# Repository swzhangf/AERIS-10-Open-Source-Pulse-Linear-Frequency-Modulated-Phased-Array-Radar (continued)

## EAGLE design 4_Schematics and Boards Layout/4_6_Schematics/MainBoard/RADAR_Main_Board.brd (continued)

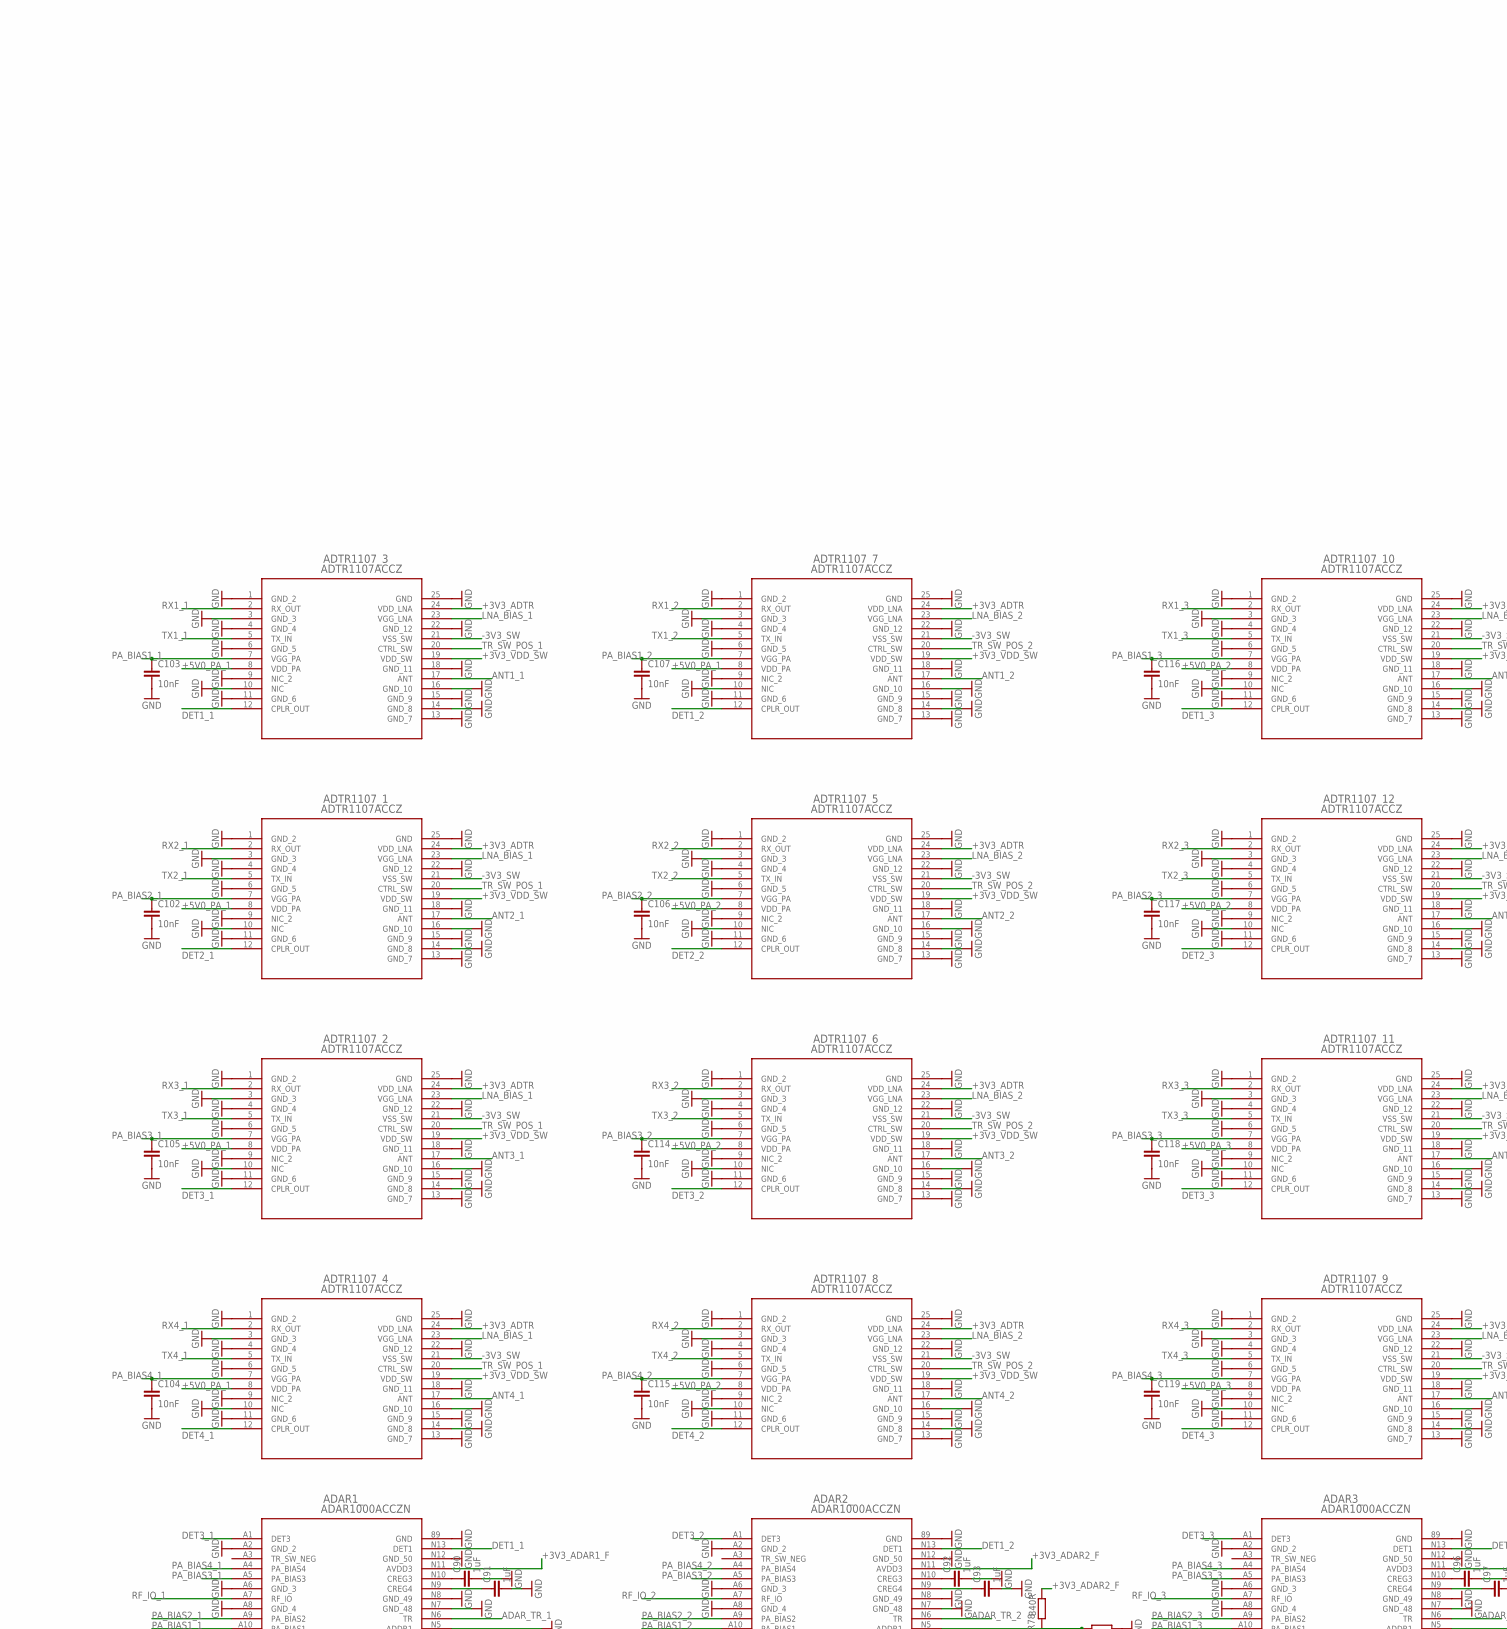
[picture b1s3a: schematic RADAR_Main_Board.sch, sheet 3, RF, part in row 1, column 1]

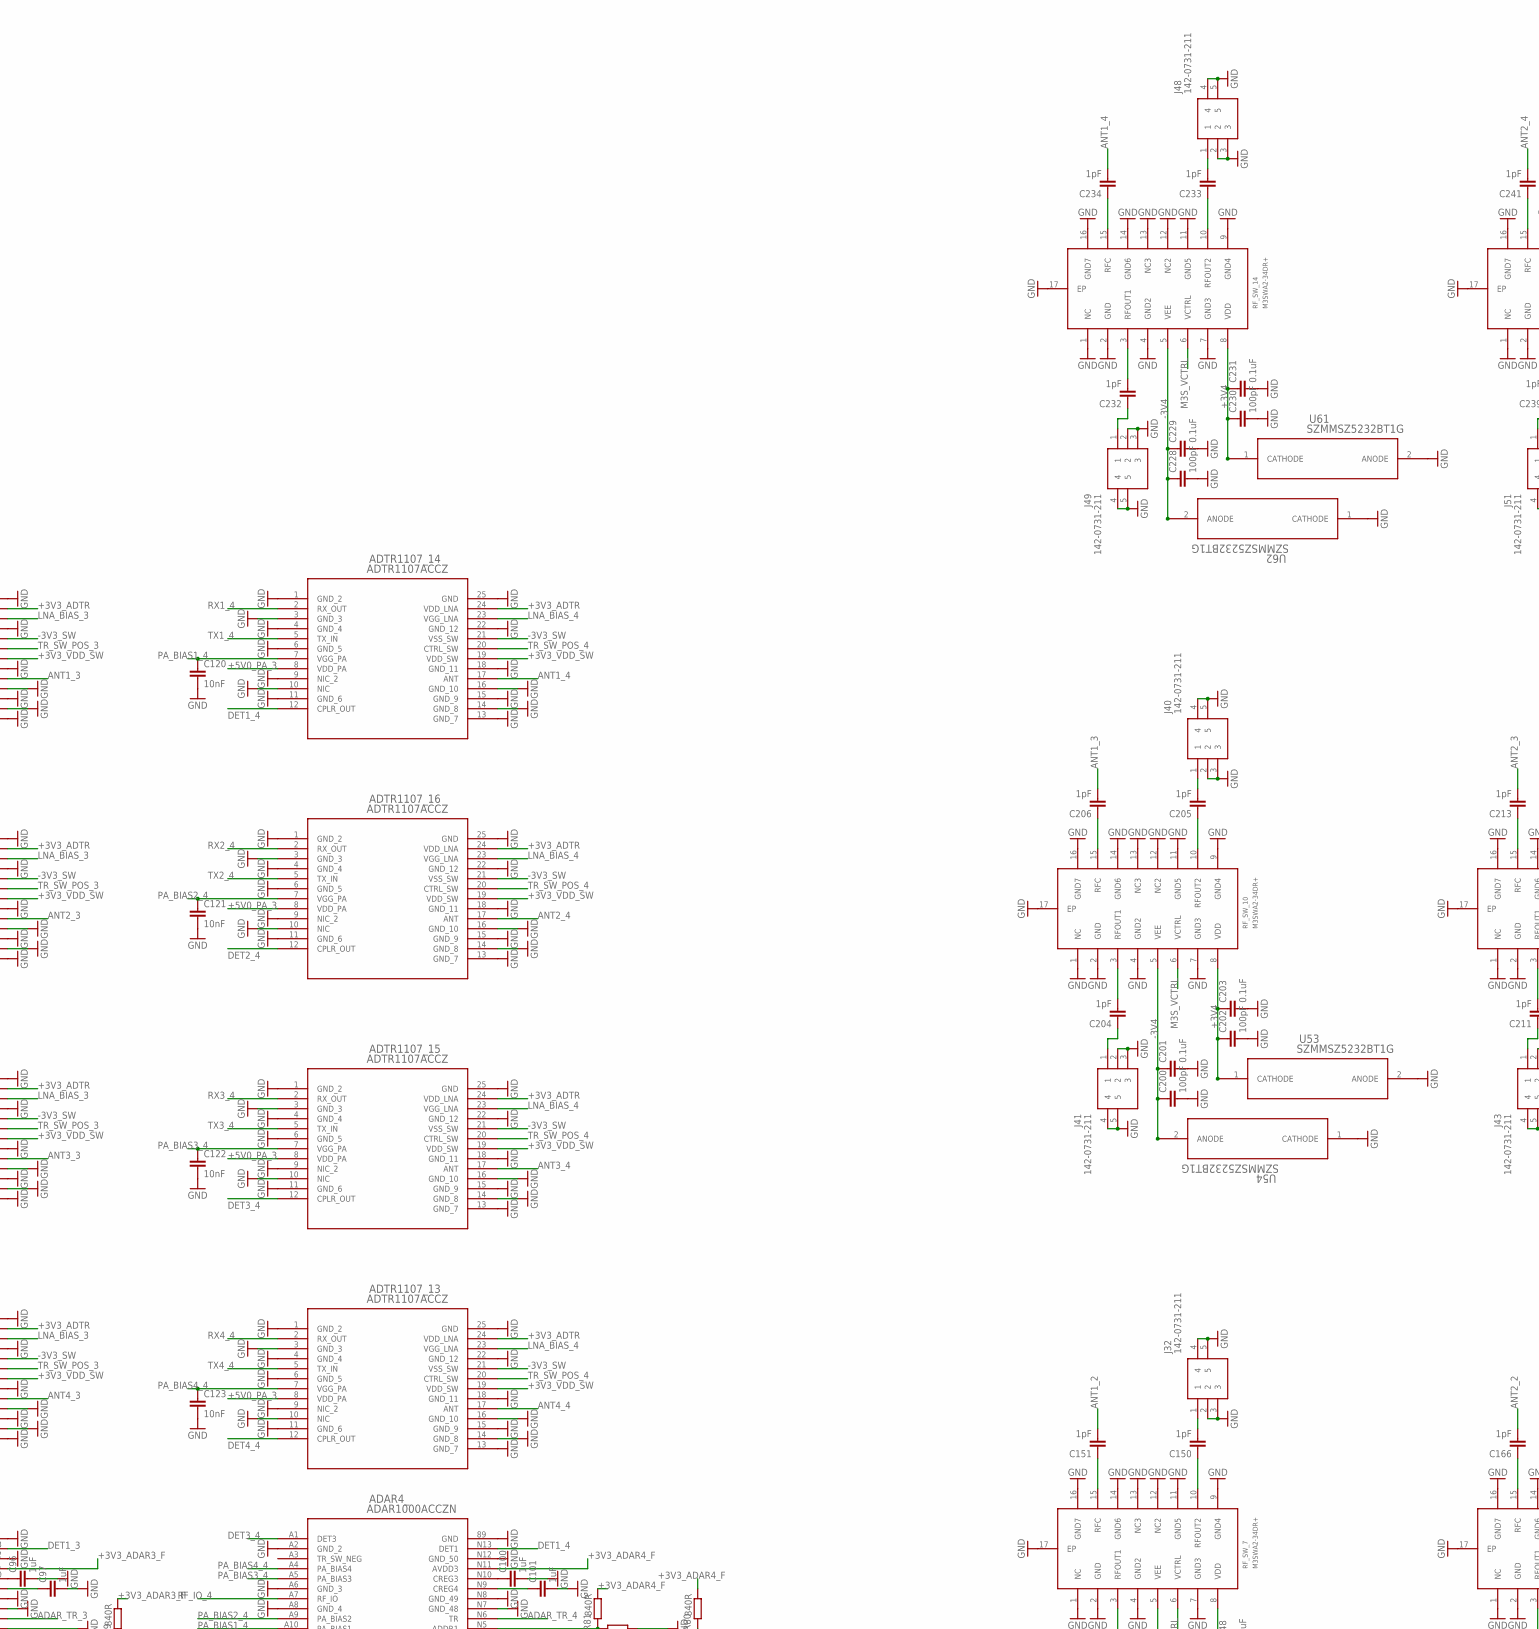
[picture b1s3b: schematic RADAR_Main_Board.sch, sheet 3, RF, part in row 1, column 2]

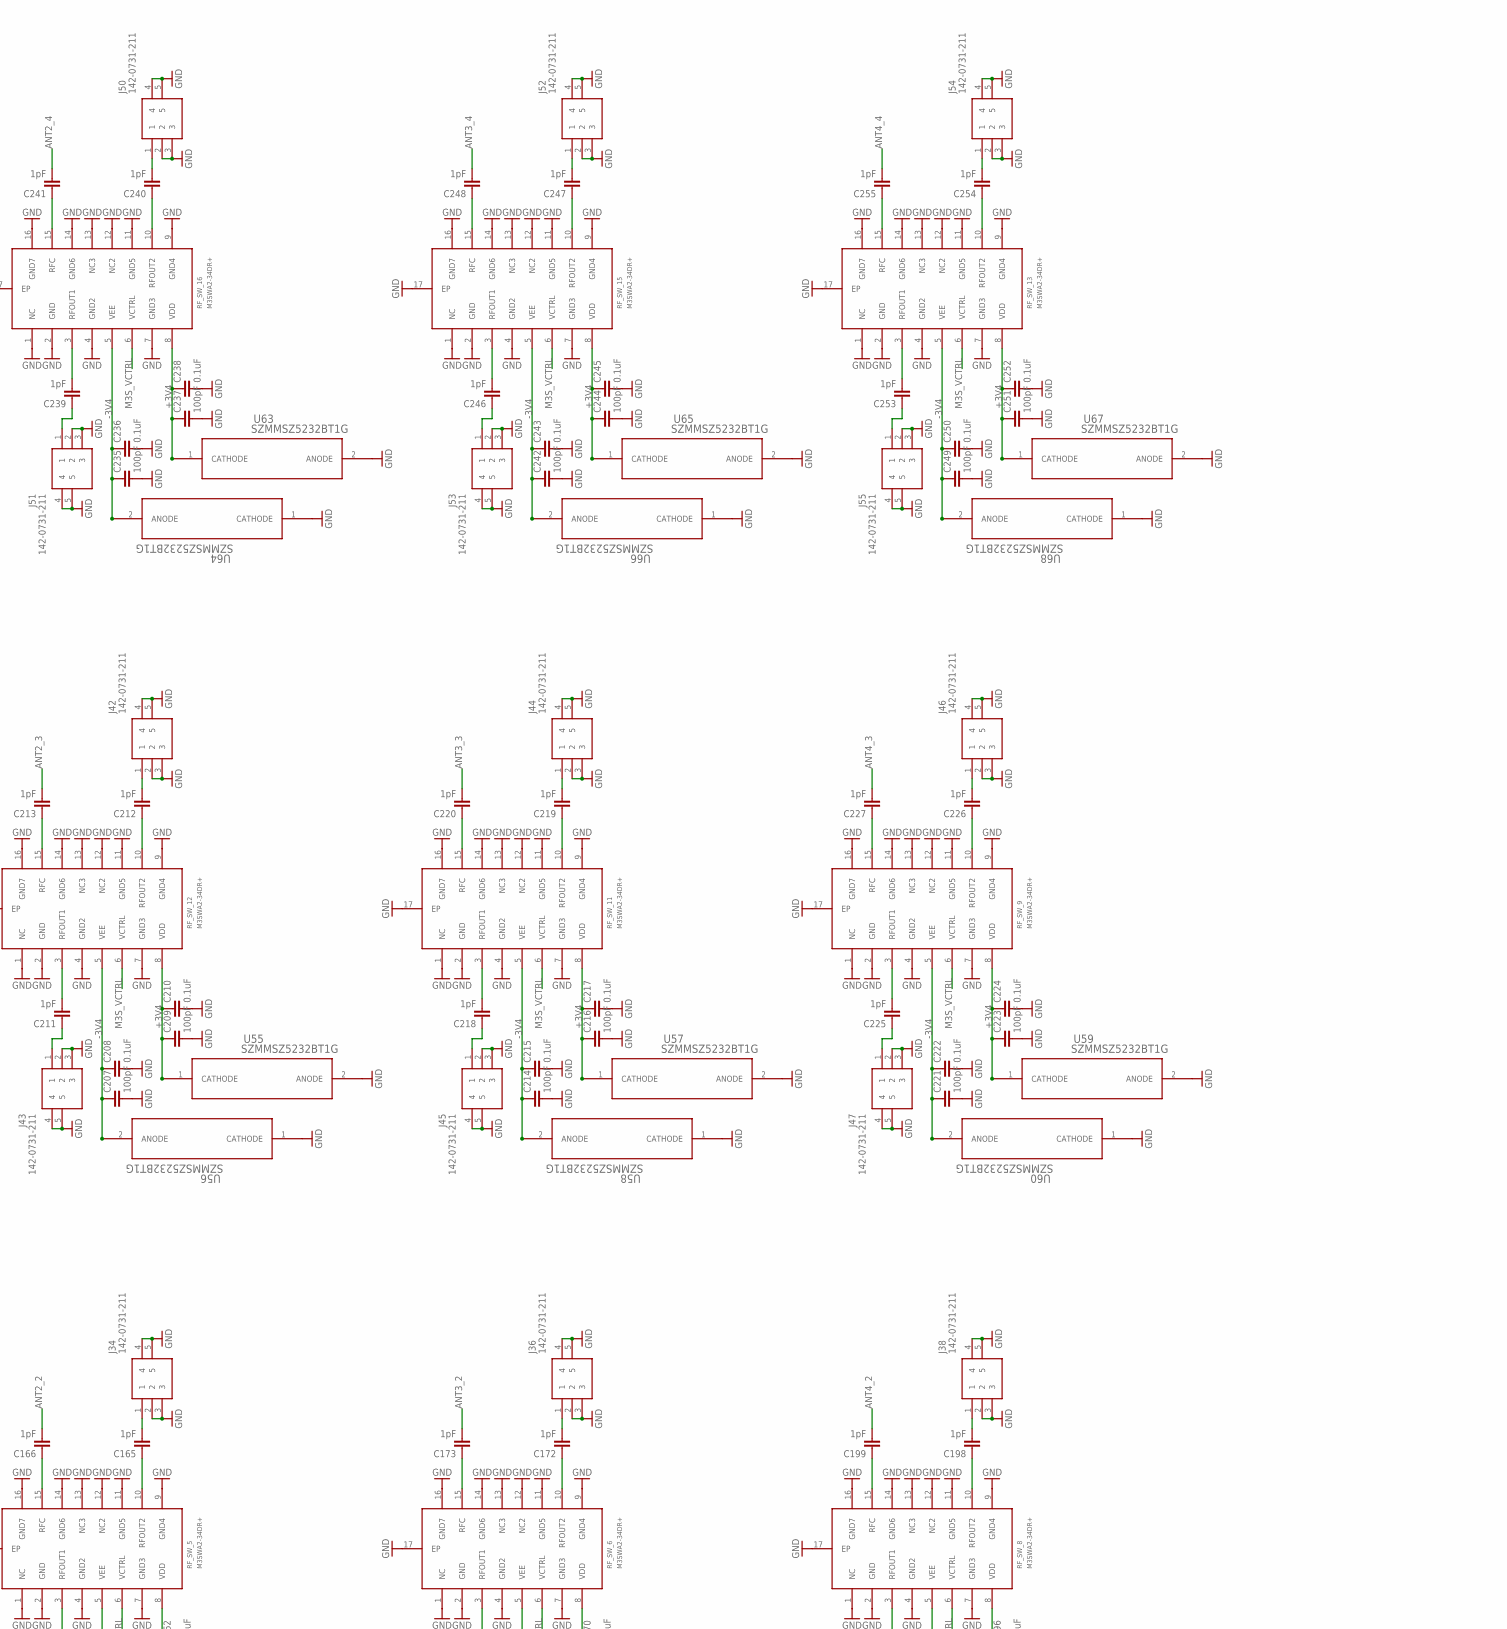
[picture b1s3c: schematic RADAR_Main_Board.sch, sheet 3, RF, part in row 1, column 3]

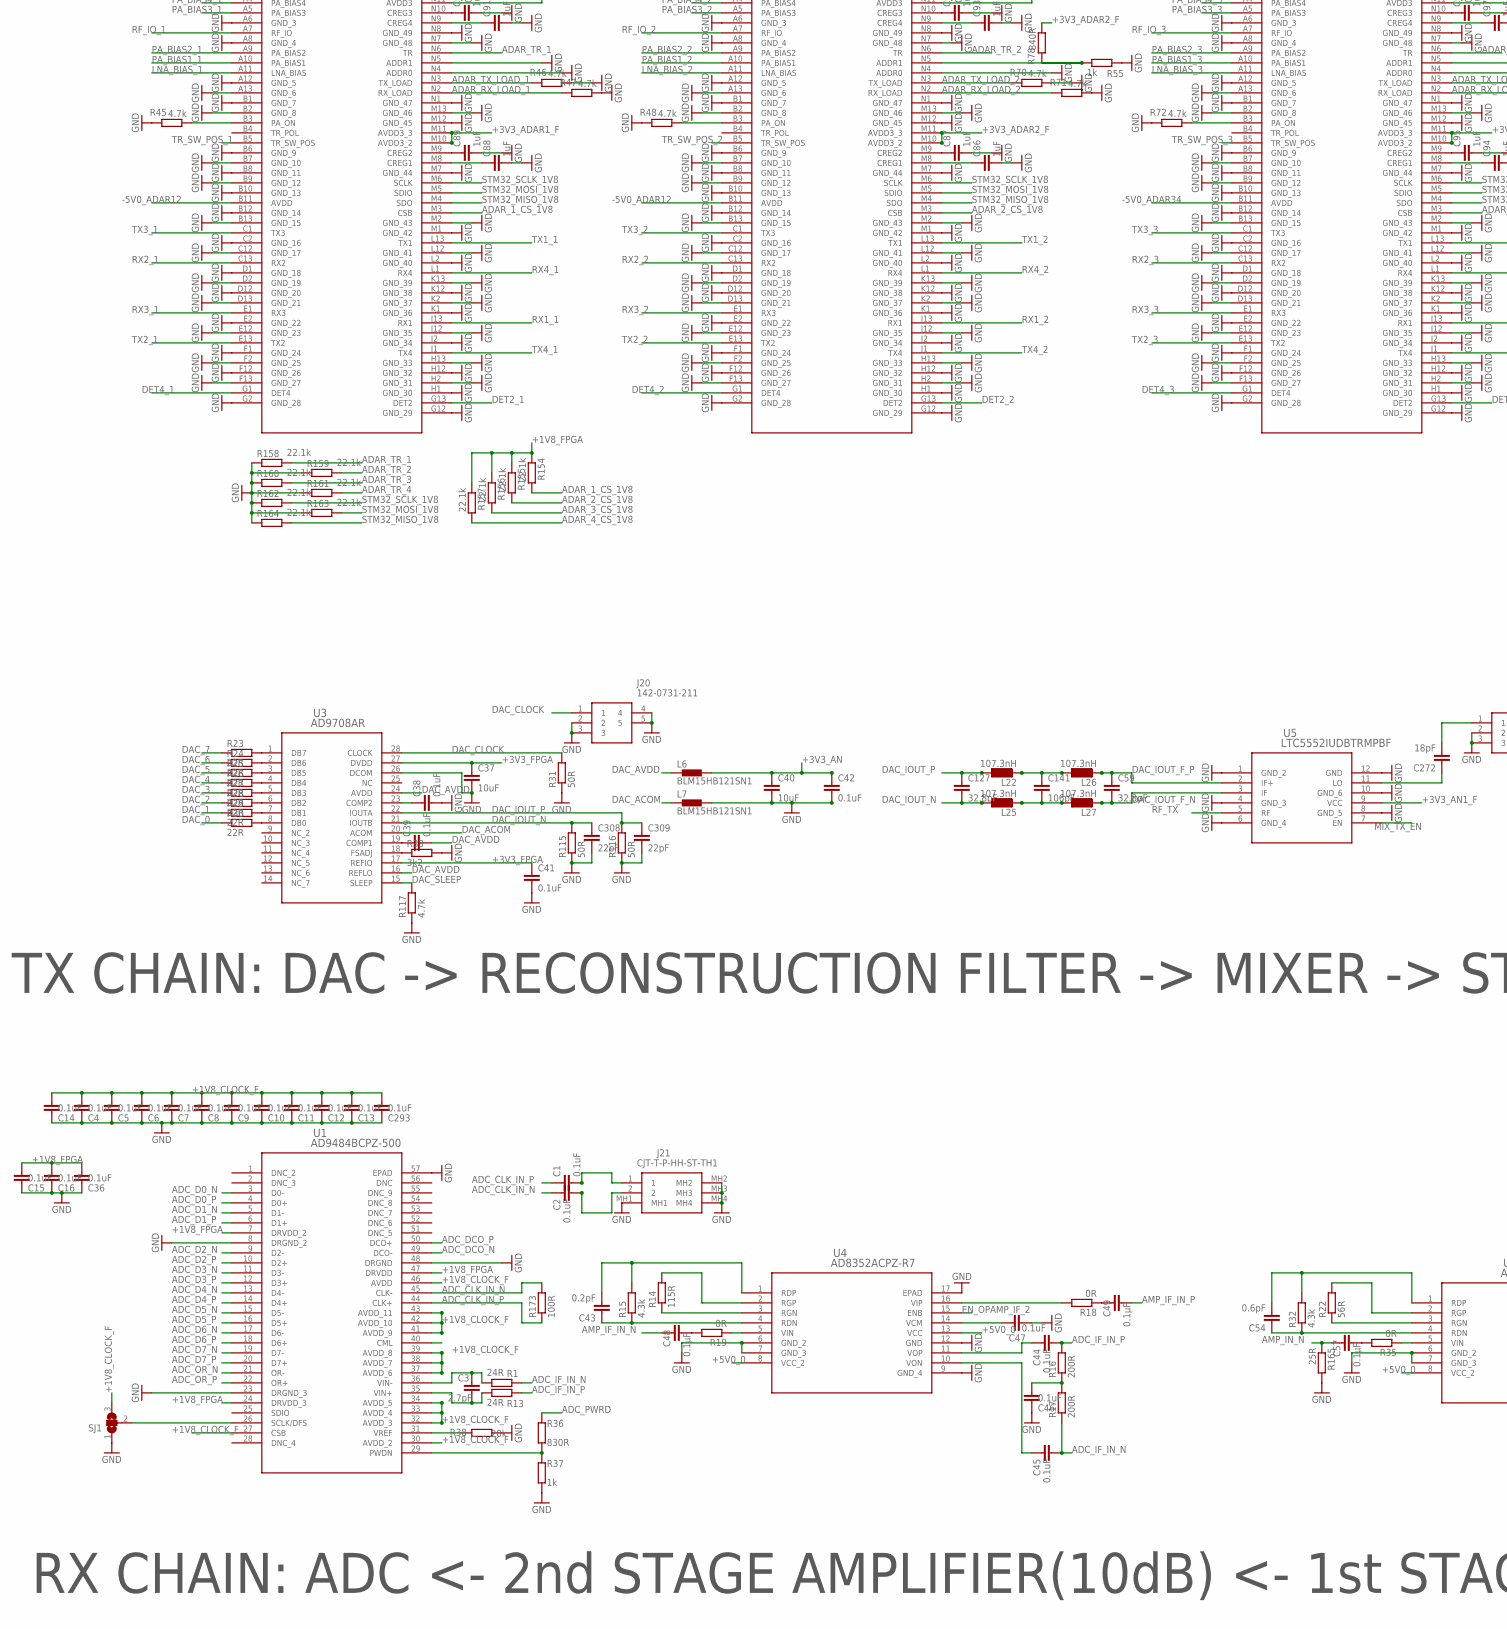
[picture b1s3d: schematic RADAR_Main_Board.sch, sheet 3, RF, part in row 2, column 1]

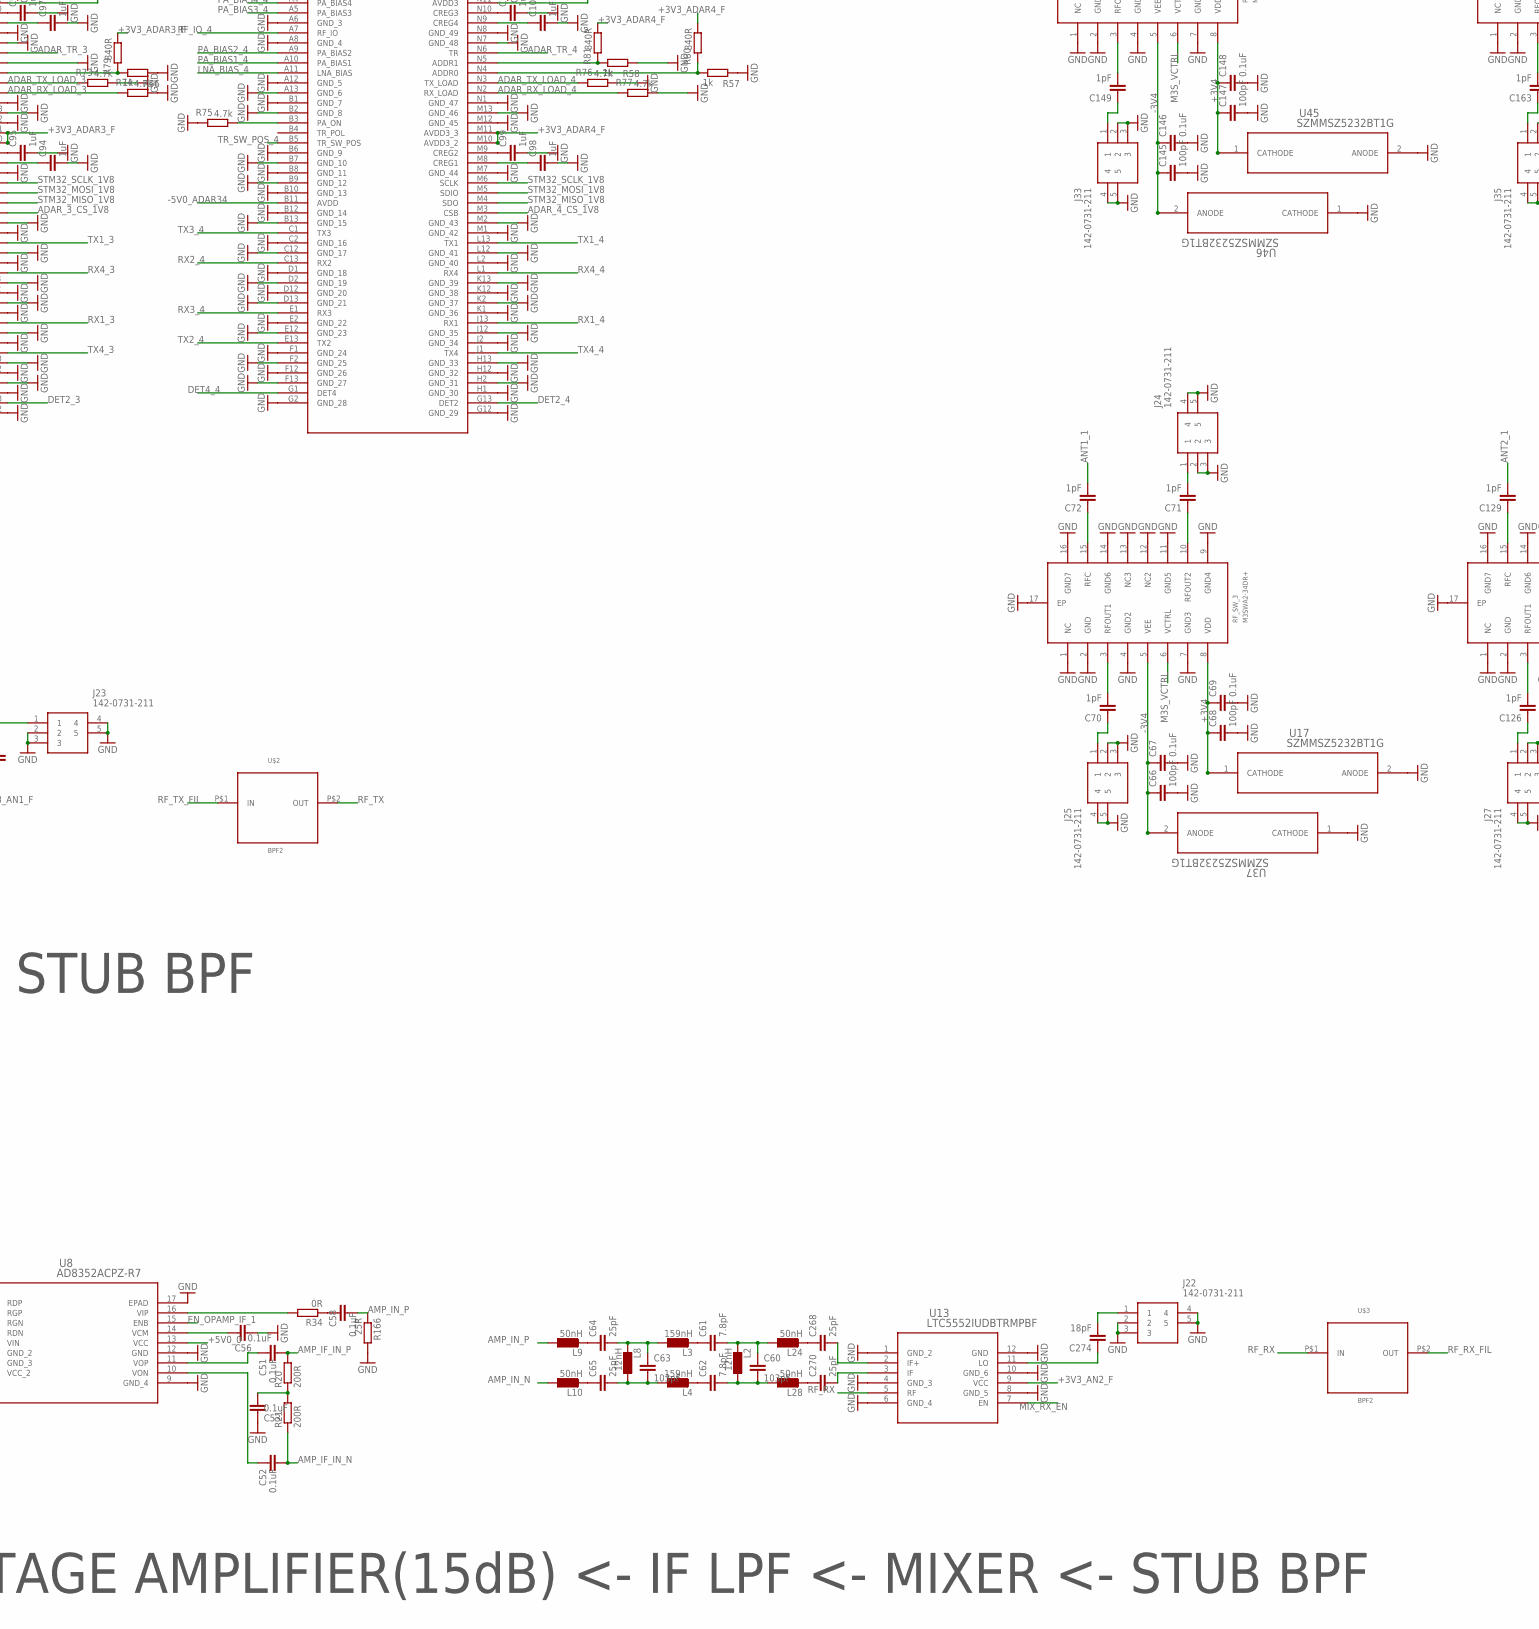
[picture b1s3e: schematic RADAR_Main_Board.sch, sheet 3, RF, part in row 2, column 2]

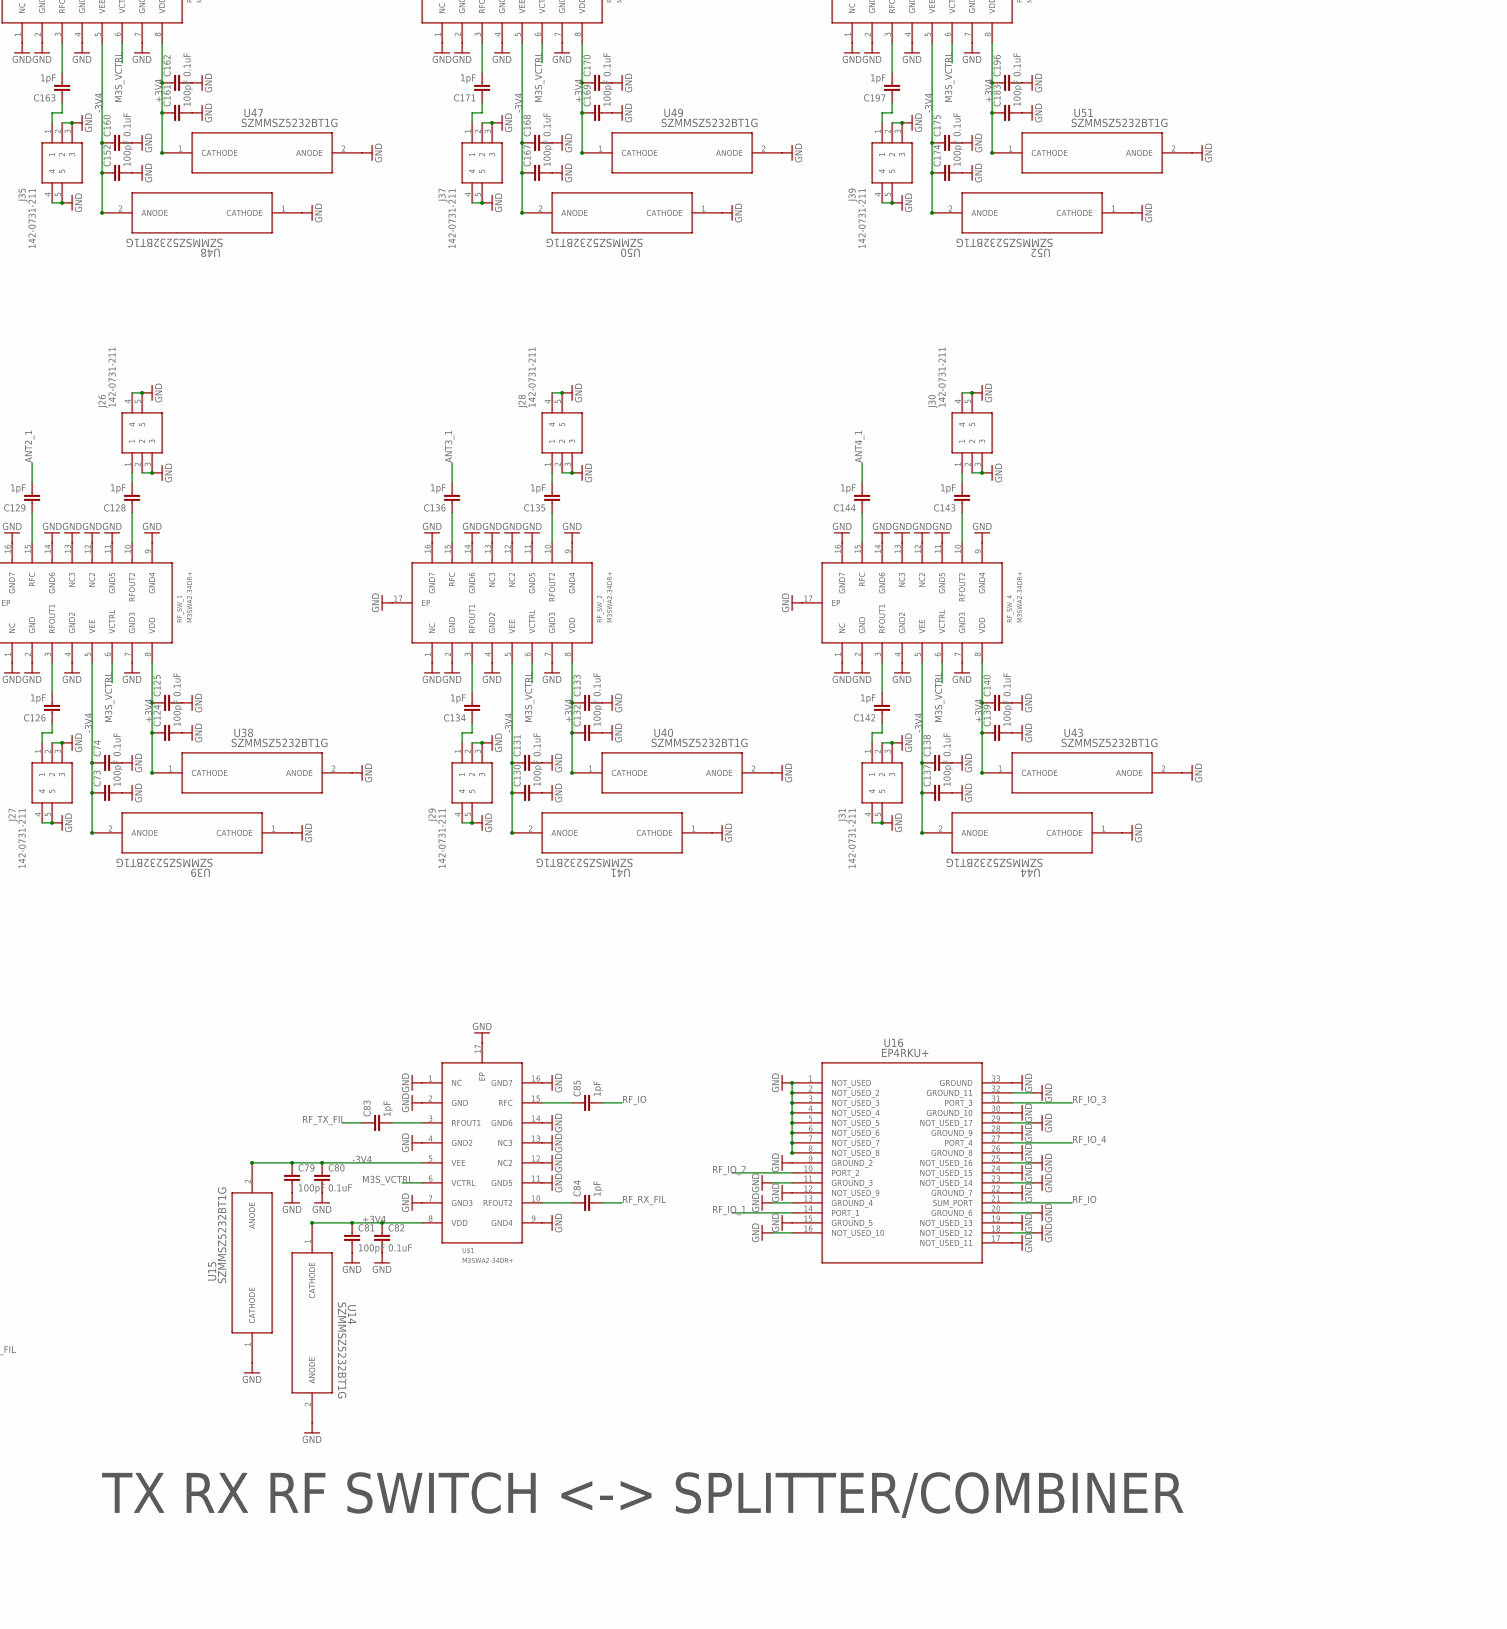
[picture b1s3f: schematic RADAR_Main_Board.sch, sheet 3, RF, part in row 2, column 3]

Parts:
ADAR1_, ADAR2_, ADAR3_, ADAR4_: ADAR1000ACCZN; CC-88-1_ADI
ADTR1107_1, ADTR1107_2, ADTR1107_3, ADTR1107_4, ADTR1107_5, ADTR1107_6, ADTR1107_7, ADTR1107_8, ADTR1107_9, ADTR1107_10, ADTR1107_11, ADTR1107_12, ADTR1107_13, ADTR1107_14, ADTR1107_15, ADTR1107_16: ADTR1107ACCZ; CC-24-8_ADI
C1, C2, C4, C5, C6, C7, C8, C9, C10, C11, C12, C13, C14, C15, C16, C36, C38, C39, C41, C42, C44, C45, C46, C47, C51, C52, C53, C56, C67, C69, C74, C80, C82, C125, C131, C133, C138, C140, C146, C148, C160, C162, C168, C170, C175, C196, C201, C203, C208, C210, C215, C217, C222, C224, C229, C231, C236, C238, C243, C245, C250, C252, C293: 0.1uF; C0201
C3: 2.7pF; C0402
C37, C40: 10uF; C0201
C43: 0.2pF; C0201
C48, C49, C57, C58: 0.1µF; C0402
C54: 0.6pF; C0201
C59, C127: 32.8pF; C0201
C60, C63: 103pF; C0201
C61, C62: 7.8pF; C0201
C64, C65, C268, C270: 25pF; C0201
C66, C68, C73, C79, C81, C124, C130, C132, C137, C139, C145, C147, C152, C161, C167, C169, C174, C183, C200, C202, C207, C209, C214, C216, C221, C223, C228, C230, C235, C237, C242, C244, C249, C251: 100pF; C0201
C70, C71, C72, C83, C84, C85, C126, C128, C129, C134, C135, C136, C142, C143, C144, C149, C150, C151, C163, C165, C166, C171, C172, C173, C197, C198, C199, C204, C205, C206, C211, C212, C213, C218, C219, C220, C225, C226, C227, C232, C233, C234, C239, C240, C241, C246, C247, C248, C253, C254, C255: 1pF; C0201
C86, C87, C88, C89, C90, C91, C92, C93, C94, C95, C96, C97, C98, C99, C100, C101: 1uF; C0201
C102, C103, C104, C105, C106, C107, C114, C115, C116, C117, C118, C119, C120, C121, C122, C123: 10nF; C0201
C141: 106pF; C0201
C272, C274: 18pF; C0201
C308, C309: 22pF; C0201
J20, J22, J23, J24, J25, J26, J27, J28, J29, J30, J31, J32, J33, J34, J35, J36, J37, J38, J39, J40, J41, J42, J43, J44, J45, J46, J47, J48, J49, J50, J51, J52, J53, J54, J55: 142-0731-211; 1420731211
J21: CJT-T-P-HH-ST-TH1; CJTTPHHSTTH1
L2, L8: 12nH; L0201
L3, L4: 159nH; L0201
L6, L7: BLM15HB121SN1; 0402
L9, L10, L24, L28: 50nH; L0201
L22, L25, L26, L27: 107.3nH; L0201
R1, R13: 24R; R0402
R14: 115R; R0201
R15, R32: 4.3k; R0201
R16, R17, R20, R21: 200R; R0201
R18, R19, R34, R35: 0R; R0201
R22: 56R; R0201
R23, R24, R25, R26, R27, R28, R29, R30: 22R; R0201
R31, R115, R116: 50R; R0201
R33: 3k2; R0201
R36: 830R; R0402
R37: 1k; R0402
R38: 20k; R0402
R45, R46, R47, R48, R70, R71, R72, R73, R74, R75, R76, R77, R117: 4.7k; R0201
R55, R56, R57, R58: 1k; R0201
R78, R79, R80, R81: 840R; R0201
R154, R155, R156, R157, R158, R159, R160, R161, R162, R163, R164: 22.1k; R0201
R165, R166: 25R; R0201
R173: 100R; R0201
RF_SW_1, RF_SW_2, RF_SW_3, RF_SW_4, RF_SW_5, RF_SW_6, RF_SW_7, RF_SW_8, RF_SW_9, RF_SW_10, RF_SW_11, RF_SW_12, RF_SW_13, RF_SW_14, RF_SW_15, RF_SW_16: M3SWA2-34DR+; 16_QFN
SJ1: SJ2W; SJ_2
U1: AD9484BCPZ-500; CP_56_5_ADI
U3: AD9708AR; RW_28_ADI
U4, U8: AD8352ACPZ-R7; CP_16_3_ADI
U5, U13: LTC5552IUDBTRMPBF; UDB_12_ADI
U14, U15, U17, U37, U38, U39, U40, U41, U43, U44, U45, U46, U47, U48, U49, U50, U51, U52, U53, U54, U55, U56, U57, U58, U59, U60, U61, U62, U63, U64, U65, U66, U67, U68: SZMMSZ5232BT1G; SOD-123_ONS
U16: EP4RKU+; DG1677-2_MNC
U$1: M3SWA2-34DR+; 16_QFN
U$2, U$3: BPF2

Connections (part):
+1V8_CLOCK_F: C4.2, C5.2, C6.2, C7.2, C8.2, C9.2, C10.2, C11.2, C12.2, C13.2, C14.2, C293.2, SJ1.3, U1.27 (CSB), U1.30 (AVDD_2), U1.32 (AVDD_3), U1.33 (AVDD_4), U1.34 (AVDD_5), U1.37 (AVDD_6), U1.38 (AVDD_7), U1.39 (AVDD_8), U1.41 (AVDD_9), U1.42 (AVDD_10), U1.43 (AVDD_11), U1.46 (AVDD); also elsewhere on the board
+1V8_FPGA: C15.2, C16.2, C36.2, R154.1, R155.1, R156.1, R157.1, U1.7 (DRVDD_2), U1.24 (DRVDD_3), U1.47 (DRVDD); also elsewhere on the board
+3V3_ADAR1_F: ADAR1_.M10 (AVDD3_2), ADAR1_.M11 (AVDD3_3), ADAR1_.N11 (AVDD3); also elsewhere on the board
+3V3_ADAR2_F: ADAR2_.M10 (AVDD3_2), ADAR2_.M11 (AVDD3_3), ADAR2_.N11 (AVDD3), R78.1; also elsewhere on the board
+3V3_ADAR3_F: ADAR3_.M10 (AVDD3_2), ADAR3_.M11 (AVDD3_3), ADAR3_.N11 (AVDD3), R79.1; also elsewhere on the board
+3V3_ADAR4_F: ADAR4_.M10 (AVDD3_2), ADAR4_.M11 (AVDD3_3), ADAR4_.N11 (AVDD3), R80.1, R81.1; also elsewhere on the board
+3V3_ADTR: ADTR1107_1.24 (VDD_LNA), ADTR1107_2.24 (VDD_LNA), ADTR1107_3.24 (VDD_LNA), ADTR1107_4.24 (VDD_LNA), ADTR1107_5.24 (VDD_LNA), ADTR1107_6.24 (VDD_LNA), ADTR1107_7.24 (VDD_LNA), ADTR1107_8.24 (VDD_LNA), ADTR1107_9.24 (VDD_LNA), ADTR1107_10.24 (VDD_LNA), ADTR1107_11.24 (VDD_LNA), ADTR1107_12.24 (VDD_LNA), ADTR1107_13.24 (VDD_LNA), ADTR1107_14.24 (VDD_LNA), ADTR1107_15.24 (VDD_LNA), ADTR1107_16.24 (VDD_LNA); also elsewhere on the board
+3V3_AN: C40.1, C42.1, L6.2; also elsewhere on the board
+3V3_AN1_F: U5.9 (VCC); also elsewhere on the board
+3V3_AN2_F: U13.9 (VCC); also elsewhere on the board
+3V3_FPGA: C37.1, C41.1, U3.17 (REFIO), U3.27 (DVDD); also elsewhere on the board
+3V3_VDD_SW: ADTR1107_1.19 (VDD_SW), ADTR1107_2.19 (VDD_SW), ADTR1107_3.19 (VDD_SW), ADTR1107_4.19 (VDD_SW), ADTR1107_5.19 (VDD_SW), ADTR1107_6.19 (VDD_SW), ADTR1107_7.19 (VDD_SW), ADTR1107_8.19 (VDD_SW), ADTR1107_9.19 (VDD_SW), ADTR1107_10.19 (VDD_SW), ADTR1107_11.19 (VDD_SW), ADTR1107_12.19 (VDD_SW), ADTR1107_13.19 (VDD_SW), ADTR1107_14.19 (VDD_SW), ADTR1107_15.19 (VDD_SW), ADTR1107_16.19 (VDD_SW); also elsewhere on the board
+3V4: C68.1, C69.1, C81.1, C82.1, C124.1, C125.1, C132.1, C133.1, C139.1, C140.1, C147.1, C148.1, C161.1, C162.1, C169.1, C170.1, C183.1, C196.1, C202.1, C203.1, C209.1, C210.1, C216.1, C217.1, C223.1, C224.1, C230.1, C231.1, C237.1, C238.1, C244.1, C245.1, C251.1, C252.1, RF_SW_1.8 (VDD), RF_SW_2.8 (VDD), RF_SW_3.8 (VDD), RF_SW_4.8 (VDD), RF_SW_5.8 (VDD), RF_SW_6.8 (VDD), RF_SW_7.8 (VDD), RF_SW_8.8 (VDD), RF_SW_9.8 (VDD), RF_SW_10.8 (VDD), RF_SW_11.8 (VDD), RF_SW_12.8 (VDD), RF_SW_13.8 (VDD), RF_SW_14.8 (VDD), RF_SW_15.8 (VDD), RF_SW_16.8 (VDD), U14.1 (CATHODE), U17.1 (CATHODE), U38.1 (CATHODE), U40.1 (CATHODE), U43.1 (CATHODE), U45.1 (CATHODE), U47.1 (CATHODE), U49.1 (CATHODE), U51.1 (CATHODE), U53.1 (CATHODE), U55.1 (CATHODE), U57.1 (CATHODE), U59.1 (CATHODE), U61.1 (CATHODE), U63.1 (CATHODE), U65.1 (CATHODE), U67.1 (CATHODE), U$1.8 (VDD); also elsewhere on the board
+5V0_0: U4.8 (VCC_2), U4.13 (VCC), U8.8 (VCC_2), U8.13 (VCC); also elsewhere on the board
+5V0_PA_1: ADTR1107_1.8 (VDD_PA), ADTR1107_2.8 (VDD_PA), ADTR1107_3.8 (VDD_PA), ADTR1107_4.8 (VDD_PA), ADTR1107_7.8 (VDD_PA); also elsewhere on the board
+5V0_PA_2: ADTR1107_5.8 (VDD_PA), ADTR1107_6.8 (VDD_PA), ADTR1107_8.8 (VDD_PA), ADTR1107_10.8 (VDD_PA), ADTR1107_12.8 (VDD_PA); also elsewhere on the board
+5V0_PA_3: ADTR1107_9.8 (VDD_PA), ADTR1107_11.8 (VDD_PA), ADTR1107_13.8 (VDD_PA), ADTR1107_14.8 (VDD_PA), ADTR1107_15.8 (VDD_PA), ADTR1107_16.8 (VDD_PA); also elsewhere on the board
-3V3_SW: ADTR1107_1.21 (VSS_SW), ADTR1107_2.21 (VSS_SW), ADTR1107_3.21 (VSS_SW), ADTR1107_4.21 (VSS_SW), ADTR1107_5.21 (VSS_SW), ADTR1107_6.21 (VSS_SW), ADTR1107_7.21 (VSS_SW), ADTR1107_8.21 (VSS_SW), ADTR1107_9.21 (VSS_SW), ADTR1107_10.21 (VSS_SW), ADTR1107_11.21 (VSS_SW), ADTR1107_12.21 (VSS_SW), ADTR1107_13.21 (VSS_SW), ADTR1107_14.21 (VSS_SW), ADTR1107_15.21 (VSS_SW), ADTR1107_16.21 (VSS_SW); also elsewhere on the board
-3V4: C66.1, C67.1, C73.1, C74.1, C79.1, C80.1, C130.1, C131.1, C137.1, C138.1, C145.1, C146.1, C152.1, C160.1, C167.1, C168.1, C174.1, C175.1, C200.1, C201.1, C207.1, C208.1, C214.1, C215.1, C221.1, C222.1, C228.1, C229.1, C235.1, C236.1, C242.1, C243.1, C249.1, C250.1, RF_SW_1.5 (VEE), RF_SW_2.5 (VEE), RF_SW_3.5 (VEE), RF_SW_4.5 (VEE), RF_SW_5.5 (VEE), RF_SW_6.5 (VEE), RF_SW_7.5 (VEE), RF_SW_8.5 (VEE), RF_SW_9.5 (VEE), RF_SW_10.5 (VEE), RF_SW_11.5 (VEE), RF_SW_12.5 (VEE), RF_SW_13.5 (VEE), RF_SW_14.5 (VEE), RF_SW_15.5 (VEE), RF_SW_16.5 (VEE), U15.2 (ANODE), U37.2 (ANODE), U39.2 (ANODE), U41.2 (ANODE), U44.2 (ANODE), U46.2 (ANODE), U48.2 (ANODE), U50.2 (ANODE), U52.2 (ANODE), U54.2 (ANODE), U56.2 (ANODE), U58.2 (ANODE), U60.2 (ANODE), U62.2 (ANODE), U64.2 (ANODE), U66.2 (ANODE), U68.2 (ANODE), U$1.5 (VEE); also elsewhere on the board
-5V0_ADAR12: ADAR1_.B11 (AVDD), ADAR2_.B11 (AVDD); also elsewhere on the board
-5V0_ADAR34: ADAR3_.B11 (AVDD), ADAR4_.B11 (AVDD); also elsewhere on the board
ADAR_1_CS_1V8: ADAR1_.M3 (CSB), R154.2; also elsewhere on the board
ADAR_2_CS_1V8: ADAR2_.M3 (CSB), R155.2; also elsewhere on the board
ADAR_3_CS_1V8: ADAR3_.M3 (CSB), R156.2; also elsewhere on the board
ADAR_4_CS_1V8: ADAR4_.M3 (CSB), R157.2; also elsewhere on the board
ADAR_RX_LOAD_1: ADAR1_.N2 (RX_LOAD), R47.2; also elsewhere on the board
ADAR_RX_LOAD_2: ADAR2_.N2 (RX_LOAD), R71.2; also elsewhere on the board
ADAR_RX_LOAD_3: ADAR3_.N2 (RX_LOAD), R74.2; also elsewhere on the board
ADAR_RX_LOAD_4: ADAR4_.N2 (RX_LOAD), R77.2; also elsewhere on the board
ADAR_TR_1: ADAR1_.N6 (TR), R158.2; also elsewhere on the board
ADAR_TR_2: ADAR2_.N6 (TR), R159.2; also elsewhere on the board
ADAR_TR_3: ADAR3_.N6 (TR), R160.2; also elsewhere on the board
ADAR_TR_4: ADAR4_.N6 (TR), R161.2; also elsewhere on the board
ADAR_TX_LOAD_1: ADAR1_.N3 (TX_LOAD), R46.2; also elsewhere on the board
ADAR_TX_LOAD_2: ADAR2_.N3 (TX_LOAD), R70.2; also elsewhere on the board
ADAR_TX_LOAD_3: ADAR3_.N3 (TX_LOAD), R73.2; also elsewhere on the board
ADAR_TX_LOAD_4: ADAR4_.N3 (TX_LOAD), R76.2; also elsewhere on the board
ADC_CLK_IN_N: C2.1, R173.2, U1.45 (CLK-)
ADC_CLK_IN_P: C1.1, R173.1, U1.44 (CLK+)
ADC_D0_N: U1.3 (D0-); also elsewhere on the board
ADC_D0_P: U1.4 (D0+); also elsewhere on the board
ADC_D1_N: U1.5 (D1-); also elsewhere on the board
ADC_D1_P: U1.6 (D1+); also elsewhere on the board
ADC_D2_N: U1.9 (D2-); also elsewhere on the board
ADC_D2_P: U1.10 (D2+); also elsewhere on the board
ADC_D3_N: U1.11 (D3-); also elsewhere on the board
ADC_D3_P: U1.12 (D3+); also elsewhere on the board
ADC_D4_N: U1.13 (D4-); also elsewhere on the board
ADC_D4_P: U1.14 (D4+); also elsewhere on the board
ADC_D5_N: U1.15 (D5-); also elsewhere on the board
ADC_D5_P: U1.16 (D5+); also elsewhere on the board
ADC_D6_N: U1.17 (D6-); also elsewhere on the board
ADC_D6_P: U1.18 (D6+); also elsewhere on the board
ADC_D7_N: U1.19 (D7-); also elsewhere on the board
ADC_D7_P: U1.20 (D7+); also elsewhere on the board
ADC_DCO_N: U1.49 (DCO-); also elsewhere on the board
ADC_DCO_P: U1.50 (DCO+); also elsewhere on the board
ADC_IF_IN_N: C45.2, R1.2, R17.1
ADC_IF_IN_P: C44.2, R13.2, R16.2
ADC_OR_N: U1.21 (OR-); also elsewhere on the board
ADC_OR_P: U1.22 (OR+); also elsewhere on the board
ADC_PWRD: R36.2; also elsewhere on the board
AMP_IF_IN_N: C48.1, C52.2, R21.1
AMP_IF_IN_P: C49.2, C51.2, R20.2
AMP_IN_N: C57.1, L10.1, R165.1
AMP_IN_P: C58.2, L9.1, R166.1
ANT1_1: ADTR1107_3.17 (ANT), C72.2
ANT1_2: ADTR1107_7.17 (ANT), C151.2
ANT1_3: ADTR1107_10.17 (ANT), C206.2
ANT1_4: ADTR1107_14.17 (ANT), C234.2
ANT2_1: ADTR1107_1.17 (ANT), C129.2
ANT2_2: ADTR1107_5.17 (ANT), C166.2
ANT2_3: ADTR1107_12.17 (ANT), C213.2
ANT2_4: ADTR1107_16.17 (ANT), C241.2
ANT3_1: ADTR1107_2.17 (ANT), C136.2
ANT3_2: ADTR1107_6.17 (ANT), C173.2
ANT3_3: ADTR1107_11.17 (ANT), C220.2
ANT3_4: ADTR1107_15.17 (ANT), C248.2
ANT4_1: ADTR1107_4.17 (ANT), C144.2
ANT4_2: ADTR1107_8.17 (ANT), C199.2
ANT4_3: ADTR1107_9.17 (ANT), C227.2
ANT4_4: ADTR1107_13.17 (ANT), C255.2
DAC_0: R30.1; also elsewhere on the board
DAC_1: R29.1; also elsewhere on the board
DAC_2: R28.1; also elsewhere on the board
DAC_3: R27.1; also elsewhere on the board
DAC_4: R26.1; also elsewhere on the board
DAC_5: R25.1; also elsewhere on the board
DAC_6: R24.1; also elsewhere on the board
DAC_7: R23.1; also elsewhere on the board
DAC_ACOM: L7.1, U3.20 (ACOM)
DAC_AVDD: C39.2, L6.1, U3.16 (REFLO), U3.24 (AVDD)
DAC_CLOCK: J20.1, R31.2, U3.28 (CLOCK)
DAC_IOUT_F_N: C59.2, L27.2, U5.3 (IF)
DAC_IOUT_F_P: C59.1, L26.2, U5.2 (IF+)
DAC_IOUT_N: C127.2, C308.1, L25.1, R115.2, U3.21 (IOUTB)
DAC_IOUT_P: C127.1, C309.1, L22.1, R116.2, U3.22 (IOUTA)
DAC_SLEEP: R117.2, U3.15 (SLEEP); also elsewhere on the board
DET1_1: ADAR1_.N13 (DET1), ADTR1107_3.12 (CPLR_OUT)
DET1_2: ADAR2_.N13 (DET1), ADTR1107_7.12 (CPLR_OUT)
DET1_3: ADAR3_.N13 (DET1), ADTR1107_10.12 (CPLR_OUT)
DET1_4: ADAR4_.N13 (DET1), ADTR1107_14.12 (CPLR_OUT)
DET2_1: ADAR1_.G13 (DET2), ADTR1107_1.12 (CPLR_OUT)
DET2_2: ADAR2_.G13 (DET2), ADTR1107_5.12 (CPLR_OUT)
DET2_3: ADAR3_.G13 (DET2), ADTR1107_12.12 (CPLR_OUT)
DET2_4: ADAR4_.G13 (DET2), ADTR1107_16.12 (CPLR_OUT)
DET3_1: ADAR1_.A1 (DET3), ADTR1107_2.12 (CPLR_OUT)
DET3_2: ADAR2_.A1 (DET3), ADTR1107_6.12 (CPLR_OUT)
DET3_3: ADAR3_.A1 (DET3), ADTR1107_11.12 (CPLR_OUT)
DET3_4: ADAR4_.A1 (DET3), ADTR1107_15.12 (CPLR_OUT)
DET4_1: ADAR1_.G1 (DET4), ADTR1107_4.12 (CPLR_OUT)
DET4_2: ADAR2_.G1 (DET4), ADTR1107_8.12 (CPLR_OUT)
DET4_3: ADAR3_.G1 (DET4), ADTR1107_9.12 (CPLR_OUT)
DET4_4: ADAR4_.G1 (DET4), ADTR1107_13.12 (CPLR_OUT)
EN_OPAMP_IF_1: U8.15 (ENB)
EN_OPAMP_IF_2: U4.15 (ENB)
GND: ADAR1_.89 (GND), ADAR1_.A2 (GND_2), ADAR1_.A6 (GND_3), ADAR1_.A8 (GND_4), ADAR1_.A12 (GND_5), ADAR1_.A13 (GND_6), ADAR1_.B1 (GND_7), ADAR1_.B2 (GND_8), ADAR1_.B6 (GND_9), ADAR1_.B7 (GND_10), ADAR1_.B8 (GND_11), ADAR1_.B9 (GND_12), ADAR1_.B10 (GND_13), ADAR1_.B12 (GND_14), ADAR1_.B13 (GND_15), ADAR1_.C2 (GND_16), ADAR1_.C12 (GND_17), ADAR1_.D1 (GND_18), ADAR1_.D2 (GND_19), ADAR1_.D12 (GND_20), ADAR1_.D13 (GND_21), ADAR1_.E2 (GND_22), ADAR1_.E12 (GND_23), ADAR1_.F1 (GND_24), ADAR1_.F2 (GND_25), ADAR1_.F12 (GND_26), ADAR1_.F13 (GND_27), ADAR1_.G2 (GND_28), ADAR1_.G12 (GND_29), ADAR1_.H1 (GND_30), ADAR1_.H2 (GND_31), ADAR1_.H12 (GND_32), ADAR1_.H13 (GND_33), ADAR1_.J2 (GND_34), ADAR1_.J12 (GND_35), ADAR1_.K1 (GND_36), ADAR1_.K2 (GND_37), ADAR1_.K12 (GND_38), ADAR1_.K13 (GND_39), ADAR1_.L2 (GND_40), ADAR1_.L12 (GND_41), ADAR1_.M1 (GND_42), ADAR1_.M2 (GND_43), ADAR1_.M7 (GND_44), ADAR1_.M12 (GND_45), ADAR1_.M13 (GND_46), ADAR1_.N1 (GND_47), ADAR1_.N4 (ADDR0), ADAR1_.N5 (ADDR1), ADAR1_.N7 (GND_48), ADAR1_.N8 (GND_49), ADAR1_.N12 (GND_50), ADAR2_.89 (GND), ADAR2_.A2 (GND_2), ADAR2_.A6 (GND_3), ADAR2_.A8 (GND_4), ADAR2_.A12 (GND_5), ADAR2_.A13 (GND_6), ADAR2_.B1 (GND_7), ADAR2_.B2 (GND_8), ADAR2_.B6 (GND_9), ADAR2_.B7 (GND_10), ADAR2_.B8 (GND_11), ADAR2_.B9 (GND_12), ADAR2_.B10 (GND_13), ADAR2_.B12 (GND_14), ADAR2_.B13 (GND_15), ADAR2_.C2 (GND_16), ADAR2_.C12 (GND_17), ADAR2_.D1 (GND_18), ADAR2_.D2 (GND_19), ADAR2_.D12 (GND_20), ADAR2_.D13 (GND_21), ADAR2_.E2 (GND_22), ADAR2_.E12 (GND_23), ADAR2_.F1 (GND_24), ADAR2_.F2 (GND_25), ADAR2_.F12 (GND_26), ADAR2_.F13 (GND_27), ADAR2_.G2 (GND_28), ADAR2_.G12 (GND_29)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; also elsewhere on the board
LNA_BIAS_1: ADAR1_.A11 (LNA_BIAS), ADTR1107_1.23 (VGG_LNA), ADTR1107_2.23 (VGG_LNA), ADTR1107_3.23 (VGG_LNA), ADTR1107_4.23 (VGG_LNA)
LNA_BIAS_2: ADAR2_.A11 (LNA_BIAS), ADTR1107_5.23 (VGG_LNA), ADTR1107_6.23 (VGG_LNA), ADTR1107_7.23 (VGG_LNA), ADTR1107_8.23 (VGG_LNA)
LNA_BIAS_3: ADAR3_.A11 (LNA_BIAS), ADTR1107_9.23 (VGG_LNA), ADTR1107_10.23 (VGG_LNA), ADTR1107_11.23 (VGG_LNA), ADTR1107_12.23 (VGG_LNA)
LNA_BIAS_4: ADAR4_.A11 (LNA_BIAS), ADTR1107_13.23 (VGG_LNA), ADTR1107_14.23 (VGG_LNA), ADTR1107_15.23 (VGG_LNA), ADTR1107_16.23 (VGG_LNA)
M3S_VCTRL: RF_SW_1.6 (VCTRL), RF_SW_2.6 (VCTRL), RF_SW_3.6 (VCTRL), RF_SW_4.6 (VCTRL), RF_SW_5.6 (VCTRL), RF_SW_6.6 (VCTRL), RF_SW_7.6 (VCTRL), RF_SW_8.6 (VCTRL), RF_SW_9.6 (VCTRL), RF_SW_10.6 (VCTRL), RF_SW_11.6 (VCTRL), RF_SW_12.6 (VCTRL), RF_SW_13.6 (VCTRL), RF_SW_14.6 (VCTRL), RF_SW_15.6 (VCTRL), RF_SW_16.6 (VCTRL), U$1.6 (VCTRL); also elsewhere on the board
MIX_RX_EN: U13.7 (EN); also elsewhere on the board
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
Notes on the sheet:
TX CHAIN: DAC -> RECONSTRUCTION FILTER -> MIXER -> STUB BPF
RX CHAIN: ADC <- 2nd STAGE AMPLIFIER(10dB) <- 1st STAGE AMPLIFIER(15dB) <- IF LPF <- MIXER <- STUB BPF
TX RX RF SWITCH <-> SPLITTER/COMBINER
